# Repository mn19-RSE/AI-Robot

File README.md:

# AI-Robot
This is a repo representing the personal robotics project I started in late 2024.  
The plan is to create a walking robot that will incorporate BLDC motors, CAN bus communication, machine vision, and AI models for object detection and decision making.

## License
This project is protected under the defualt copyright laws. I retain all rights to the source code created by me and no one may reproduce, distribute, or create derivative original works from this project.

## Contained Files
- 3D CAD models
- Arduino code for motion control
- ML code for machine vision and decisinon making 
- BOM

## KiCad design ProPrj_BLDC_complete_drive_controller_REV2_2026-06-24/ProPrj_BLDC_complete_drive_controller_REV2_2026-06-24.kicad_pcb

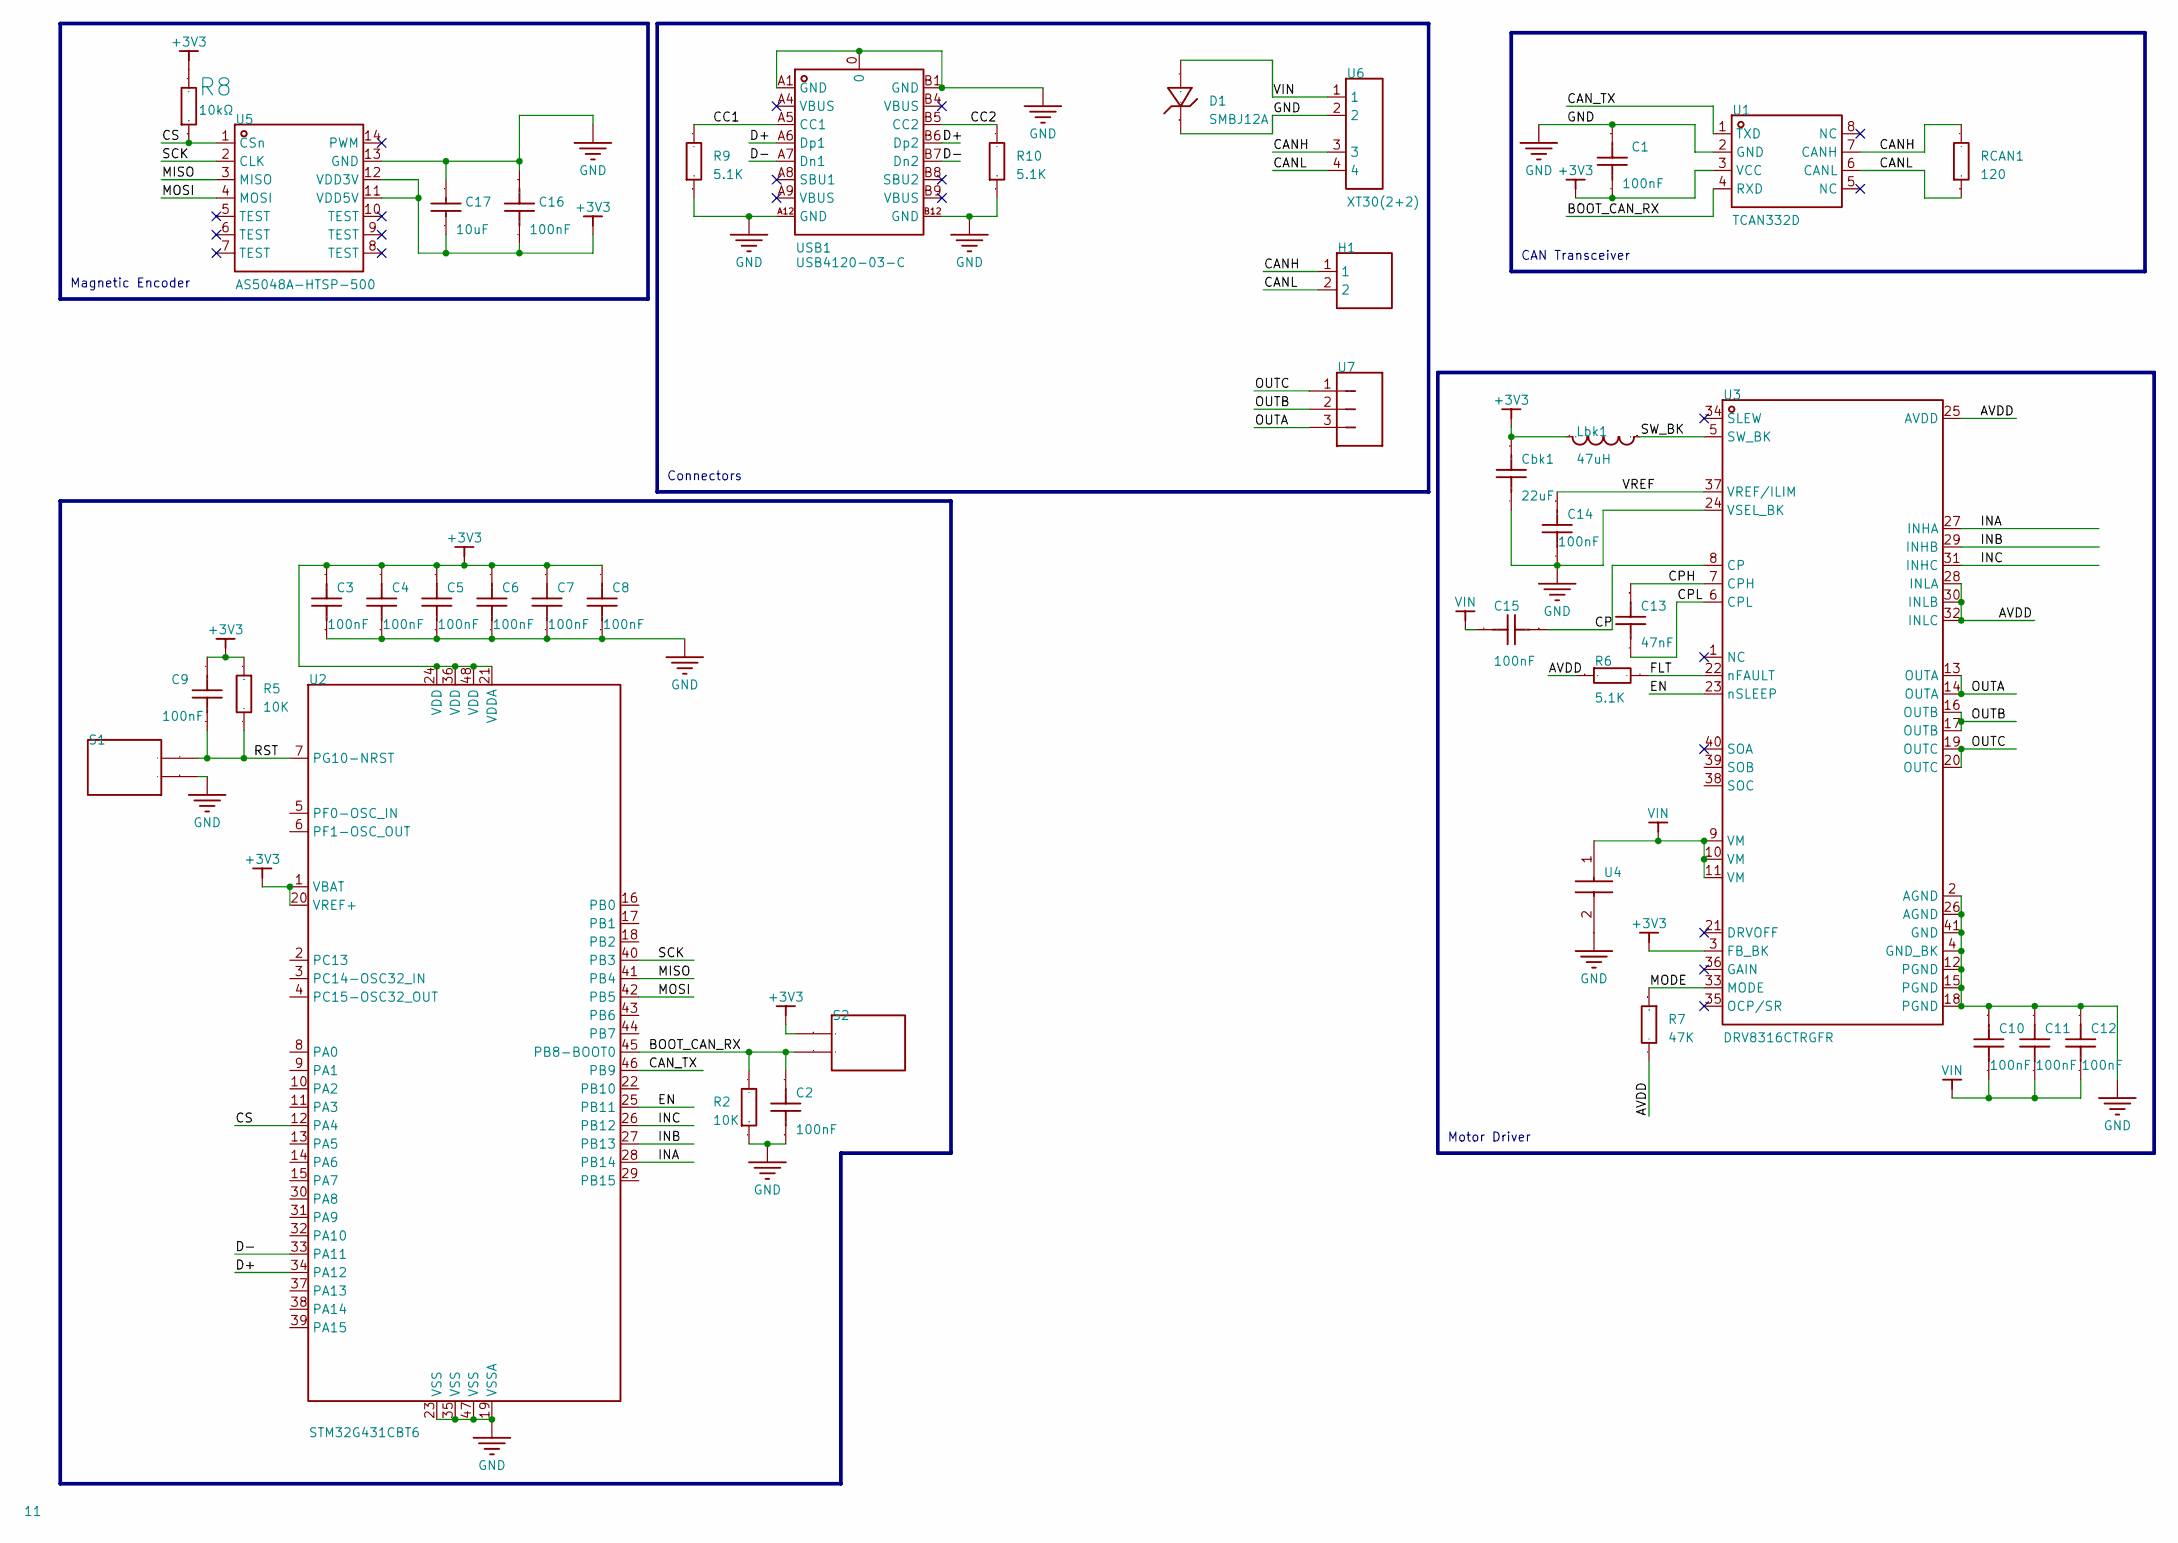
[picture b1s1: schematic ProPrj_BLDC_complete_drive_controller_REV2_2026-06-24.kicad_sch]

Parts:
11: (no value)
C1, C2, C3, C4, C5, C6, C7, C8, C9, C10, C11, C12, C14, C15: 100nF; C0603
C13: 47nF; C0603
C16: 100nF; C0603; Tolerance ±10%; Voltage Rating 50V; Manufacturer Part CC0603KRX7R9BB104; LCSC Part Name 100nF ±10% 50V
C17: 10uF; C0402; Tolerance ±20%; Voltage Rating 6.3V; Manufacturer Part CL05A106MQ5NUNC; LCSC Part Name 10uF ±20% 6.3V
Cbk1: 22uF; C0603
D1: SMBJ12A; SMB_L4.6-W3.6-LS5.3-RD; Manufacturer Part SMBJ12A; LCSC Part Name SMBJ12A
H1: HDR-TH_2P-P2.54-V-M-1
Lbk1: 47uH; L0805
R2, R5: 10K; R0402
R6, R9, R10: 5.1K; R0402
R7: 47K; R0402
R8: 10kΩ; R0603; Tolerance ±1%; Voltage-Supply(Max) 75V; Manufacturer Part 0603WAF1002T5E; LCSC Part Name 厚膜电阻 10kΩ ±1% 100mW
RCAN1: 120; R0402
S1, S2: 95C04A3GWRT
U1: TCAN332D; SOIC-8_L4.9-W3.9-P1.27-LS6.0-BL; Supply Voltage 3V~3.6V; Manufacturer Part TCAN332D; LCSC Part Name TCAN332D
U2: STM32G431CBT6; LQFP-48_L7.0-W7.0-P0.50-LS9.0-BL; Voltage - Supply 1.71V~3.6V; Manufacturer Part STM32G431CBT6; LCSC Part Name 带DSP和FPU的170MHz主流ARM Cortex-M4 MCU，具有12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
U3: DRV8316CTRGFR; VQFN-40_L7.0-W5.0-P0.50-TL-EP5.7; Manufacturer Part DRV8316CTRGFR; LCSC Part Name DRV8316C 三相集成FET电机驱动器
U4: aha0608470m035r; CAPAE660X850N
U5: AS5048A-HTSP-500; TSSOP-14_L5.0-W4.4-P0.65-LS6.4-BL; Voltage - Supply 3V~3.6V；4.5V~5.5V; Manufacturer Part AS5048A-HTSP-500; LCSC Part Name AS5048A-HTSP-500
U6: XT30(2+2); CONN-TH_XT30-2-2; Manufacturer Part XT30(2+2); LCSC Part Name XT30(2+2)
U7: SCREWTERMINAL-3.5MM-3
USB1: USB4120-03-C; TYPE-C-SMD_USB4120-03-C; Manufacturer Part USB4120-03-C; LCSC Part Name Type-C 母

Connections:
+3V3: C1.2, C3.2, C4.2, C5.2, C6.2, C7.2, C8.2, C9.2, C16.2, C17.1, Cbk1.1, Lbk1.2, R5.1, R8.2, S2.1, U1.3 (VCC), U2.1 (VBAT), U2.20 (VREF+), U2.21 (VDDA), U2.24 (VDD), U2.36 (VDD), U2.48 (VDD), U3.3 (FB_BK), U5.11 (VDD5V), U5.12 (VDD3V); also elsewhere on the board
AVDD: R6.1, R7.2, U3.25 (AVDD), U3.28 (INLA), U3.30 (INLB), U3.32 (INLC)
BOOT_CAN_RX: C2.2, R2.2, S2.2, U1.4 (RXD), U2.45 (PB8-BOOT0)
CANH: H1.1, RCAN1.2, U1.7 (CANH), U6.3; also elsewhere on the board
CANL: H1.2, RCAN1.1, U1.6 (CANL), U6.4; also elsewhere on the board
CAN_TX: U1.1 (TXD), U2.46 (PB9)
CC1: R9.2, USB1.A5 (CC1)
CC2: R10.2, USB1.B5 (CC2)
CP: C15.1, U3.8 (CP)
CPH: C13.1, U3.7 (CPH)
CPL: C13.2, U3.6 (CPL)
CS: R8.1, U2.12 (PA4), U5.1 (CSn)
D+: U2.34 (PA12), USB1.A6 (Dp1), USB1.B6 (Dp2)
D-: U2.33 (PA11), USB1.A7 (Dn1), USB1.B7 (Dn2)
EN: U2.25 (PB11), U3.23 (nSLEEP)
FLT: R6.2, U3.22 (nFAULT)
GND: C1.1, C2.1, C3.1, C4.1, C5.1, C6.1, C7.1, C8.1, C10.1, C11.1, C12.1, C14.2, C16.1, C17.2, Cbk1.2, D1.1 (C), R2.1, R9.1, R10.1, S1.1, U1.2 (GND), U2.19 (VSSA), U2.23 (VSS), U2.35 (VSS), U2.47 (VSS), U3.2 (AGND), U3.4 (GND_BK), U3.12 (PGND), U3.15 (PGND), U3.18 (PGND), U3.24 (VSEL_BK), U3.26 (AGND), U3.41 (GND), U4.2, U5.13 (GND), U6.2, USB1.0, USB1.A1 (GND), USB1.A12 (GND), USB1.B1 (GND), USB1.B12 (GND); also elsewhere on the board
INA: U2.28 (PB14), U3.27 (INHA)
INB: U2.27 (PB13), U3.29 (INHB)
INC: U2.26 (PB12), U3.31 (INHC)
MISO: U2.41 (PB4), U5.3 (MISO)
MODE: R7.1, U3.33 (MODE)
MOSI: U2.42 (PB5), U5.4 (MOSI)
OUTA: U3.13 (OUTA), U3.14 (OUTA), U7.3
OUTB: U3.16 (OUTB), U3.17 (OUTB), U7.2
OUTC: U3.19 (OUTC), U3.20 (OUTC), U7.1
RST: C9.1, R5.2, S1.2, U2.7 (PG10-NRST)
SCK: U2.40 (PB3), U5.2 (CLK)
SW_BK: Lbk1.1, U3.5 (SW_BK); also elsewhere on the board
VIN: C10.2, C11.2, C12.2, C15.2, D1.2 (A), U3.9 (VM), U3.10 (VM), U3.11 (VM), U4.1, U6.1
VREF: C14.1, U3.37 (VREF/ILIM)

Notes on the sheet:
Magnetic Encoder
Connectors
CAN Transceiver
Motor Driver

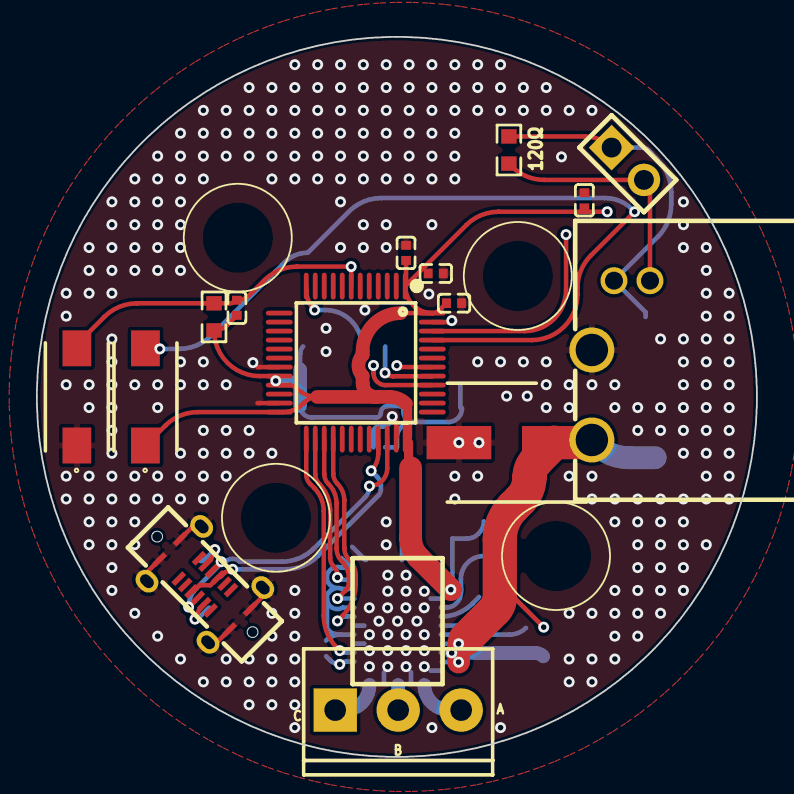
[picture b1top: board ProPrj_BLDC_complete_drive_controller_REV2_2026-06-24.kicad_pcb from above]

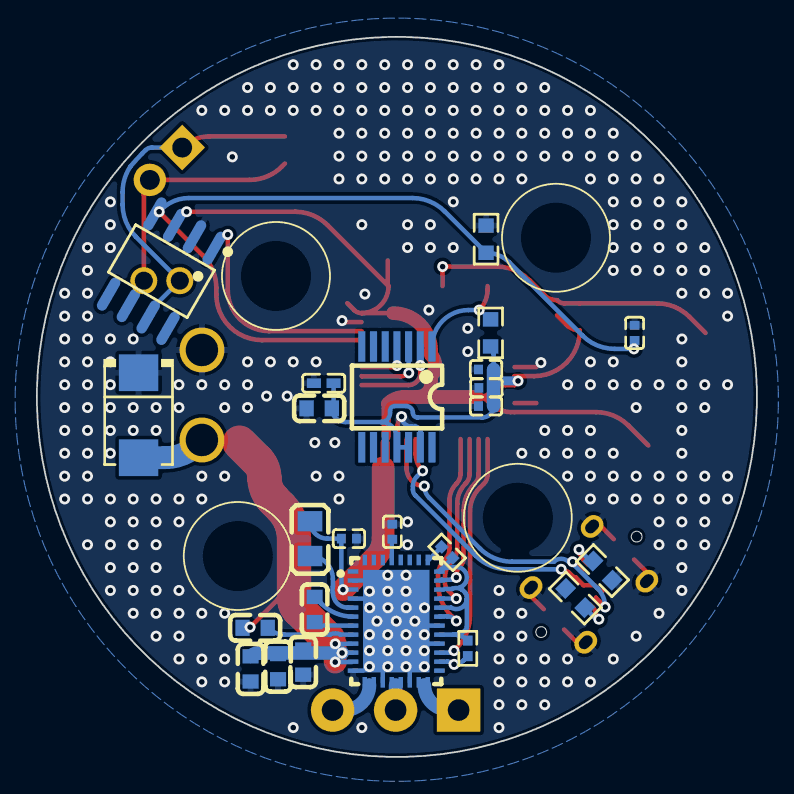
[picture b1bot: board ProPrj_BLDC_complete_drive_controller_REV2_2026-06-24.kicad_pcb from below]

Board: 2 copper layers, 40.0 x 40.0 mm, 39 parts (24 on the bottom side), 31 nets.

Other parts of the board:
Cbk: C0402
Lbk: L0805
RCAN: R0603

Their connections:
+3V3: Cbk.1, Lbk.2; also elsewhere on the board
CANH: RCAN.2; also elsewhere on the board
CANL: RCAN.1; also elsewhere on the board
GND: Cbk.2; also elsewhere on the board
SW_BK: Lbk.1; also elsewhere on the board

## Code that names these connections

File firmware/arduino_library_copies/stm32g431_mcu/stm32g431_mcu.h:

//stm32g431_mcu.h

#pragma once
using Pin = decltype(PA4);

// Motor driver
constexpr Pin MOTOR_INA = PA14;
constexpr Pin MOTOR_INB = PA13;
constexpr Pin MOTOR_INC = PA12;
constexpr Pin MOTOR_EN = PB11;

// Encoder
constexpr Pin ENC_CS = PA4;
constexpr Pin ENC_MOSI = PB5;
constexpr Pin ENC_MISO = PB4;
constexpr Pin ENC_SCK = PB3;

// CAN bus
constexpr Pin CANRX = PB8;
constexpr Pin CANTX = PB9;

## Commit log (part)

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2025-01-30 Added a line to the README.md to test the commit and push actions.
2025-01-30 Updated README.md with short description of project.
2025-01-30 Updated README.md with more project details and basic outline of repo
2025-01-30 Added .STEP file for the Nvidia Jetson Nano board and changed the license wording in the README.md file.
2025-01-30 Revert "Added .STEP file for the Nvidia Jetson Nano board and changed the license wording in the README.md file."
    This reverts commit 95083d1c199bfb8f5f54fe240bfbd90db571ed1f.
2025-01-30 Added the .STEP file for the Nvidia jetson Nano.
2025-01-30 Altered wording of licesne section.
2025-01-30 README.md formatting updates.
2025-02-03 Added SimpleFOC mini .STEP file.
2025-02-06 Added hardware documentation and verified working test programs for teh Teensy4.0+SimpleFOC mini+AS5047p adapterboard setup.
2025-02-06 Upload circuit used for BLDC_motor_SimpleFOC_angle_control_teensy4.0_test.
2025-02-06 UPdated Teensy4.0 SImplFOC angle control code.
2025-02-18 Uploaded code for multiple motor control.
2025-02-19 Updated working CAN bus tests.
2025-02-21 Added DRV8302 reference image.
2025-03-06 Added Project notes Obsidian vault
2025-03-10 Updated movement loop and set PID values to default.
2025-03-11 New movement method in timed_move.
2025-03-16 First visualization of hexapod robot.
2025-03-19 Manual for STM32 based driver alternative.
2025-06-18 Fixed ...timed_move code
2025-06-27 Uploaded DRV8302 Pinout Reference.
2025-06-27 Uploaded pinout for plug for AS5047P encoder.
2025-07-04 Created more hardware config tests.
2025-09-23 Upload block diagram for custom all-in-one controller, driver, encoder board.
2025-10-09 First iteration of custom driver and encoder.
2025-11-19 updated 11-18-2025
2026-02-16 STM32 ESC pcb files
2026-04-28 added odrive schematic for reference for DRIVER REV3
2026-05-25 Created new basic test software for DRV8316 rev2
2026-06-20 orginizing project files and removing unused documents
2026-06-20 changed folder name to schematic
2026-06-21 finished V1 of isolated test boards for driver, encoder, MCU
2026-06-22 REV1 of all boards complete
2026-06-22 old docs from work PC
2026-06-25 adding datasheets and manuals
2026-06-25 kicad project files
2026-06-27 starting CAN tests on jetson
2026-06-27 esp32s3 CAN bus circuitpython code copy
2026-06-28 working simple test of esp32s3 CAN listen
2026-06-29 trying to update the simple CAN bus python sender
2026-06-29 restructured project folders
2026-06-29 removing project notes folder
2026-06-30 reorg, made an arduino library for custom STM32 pins
